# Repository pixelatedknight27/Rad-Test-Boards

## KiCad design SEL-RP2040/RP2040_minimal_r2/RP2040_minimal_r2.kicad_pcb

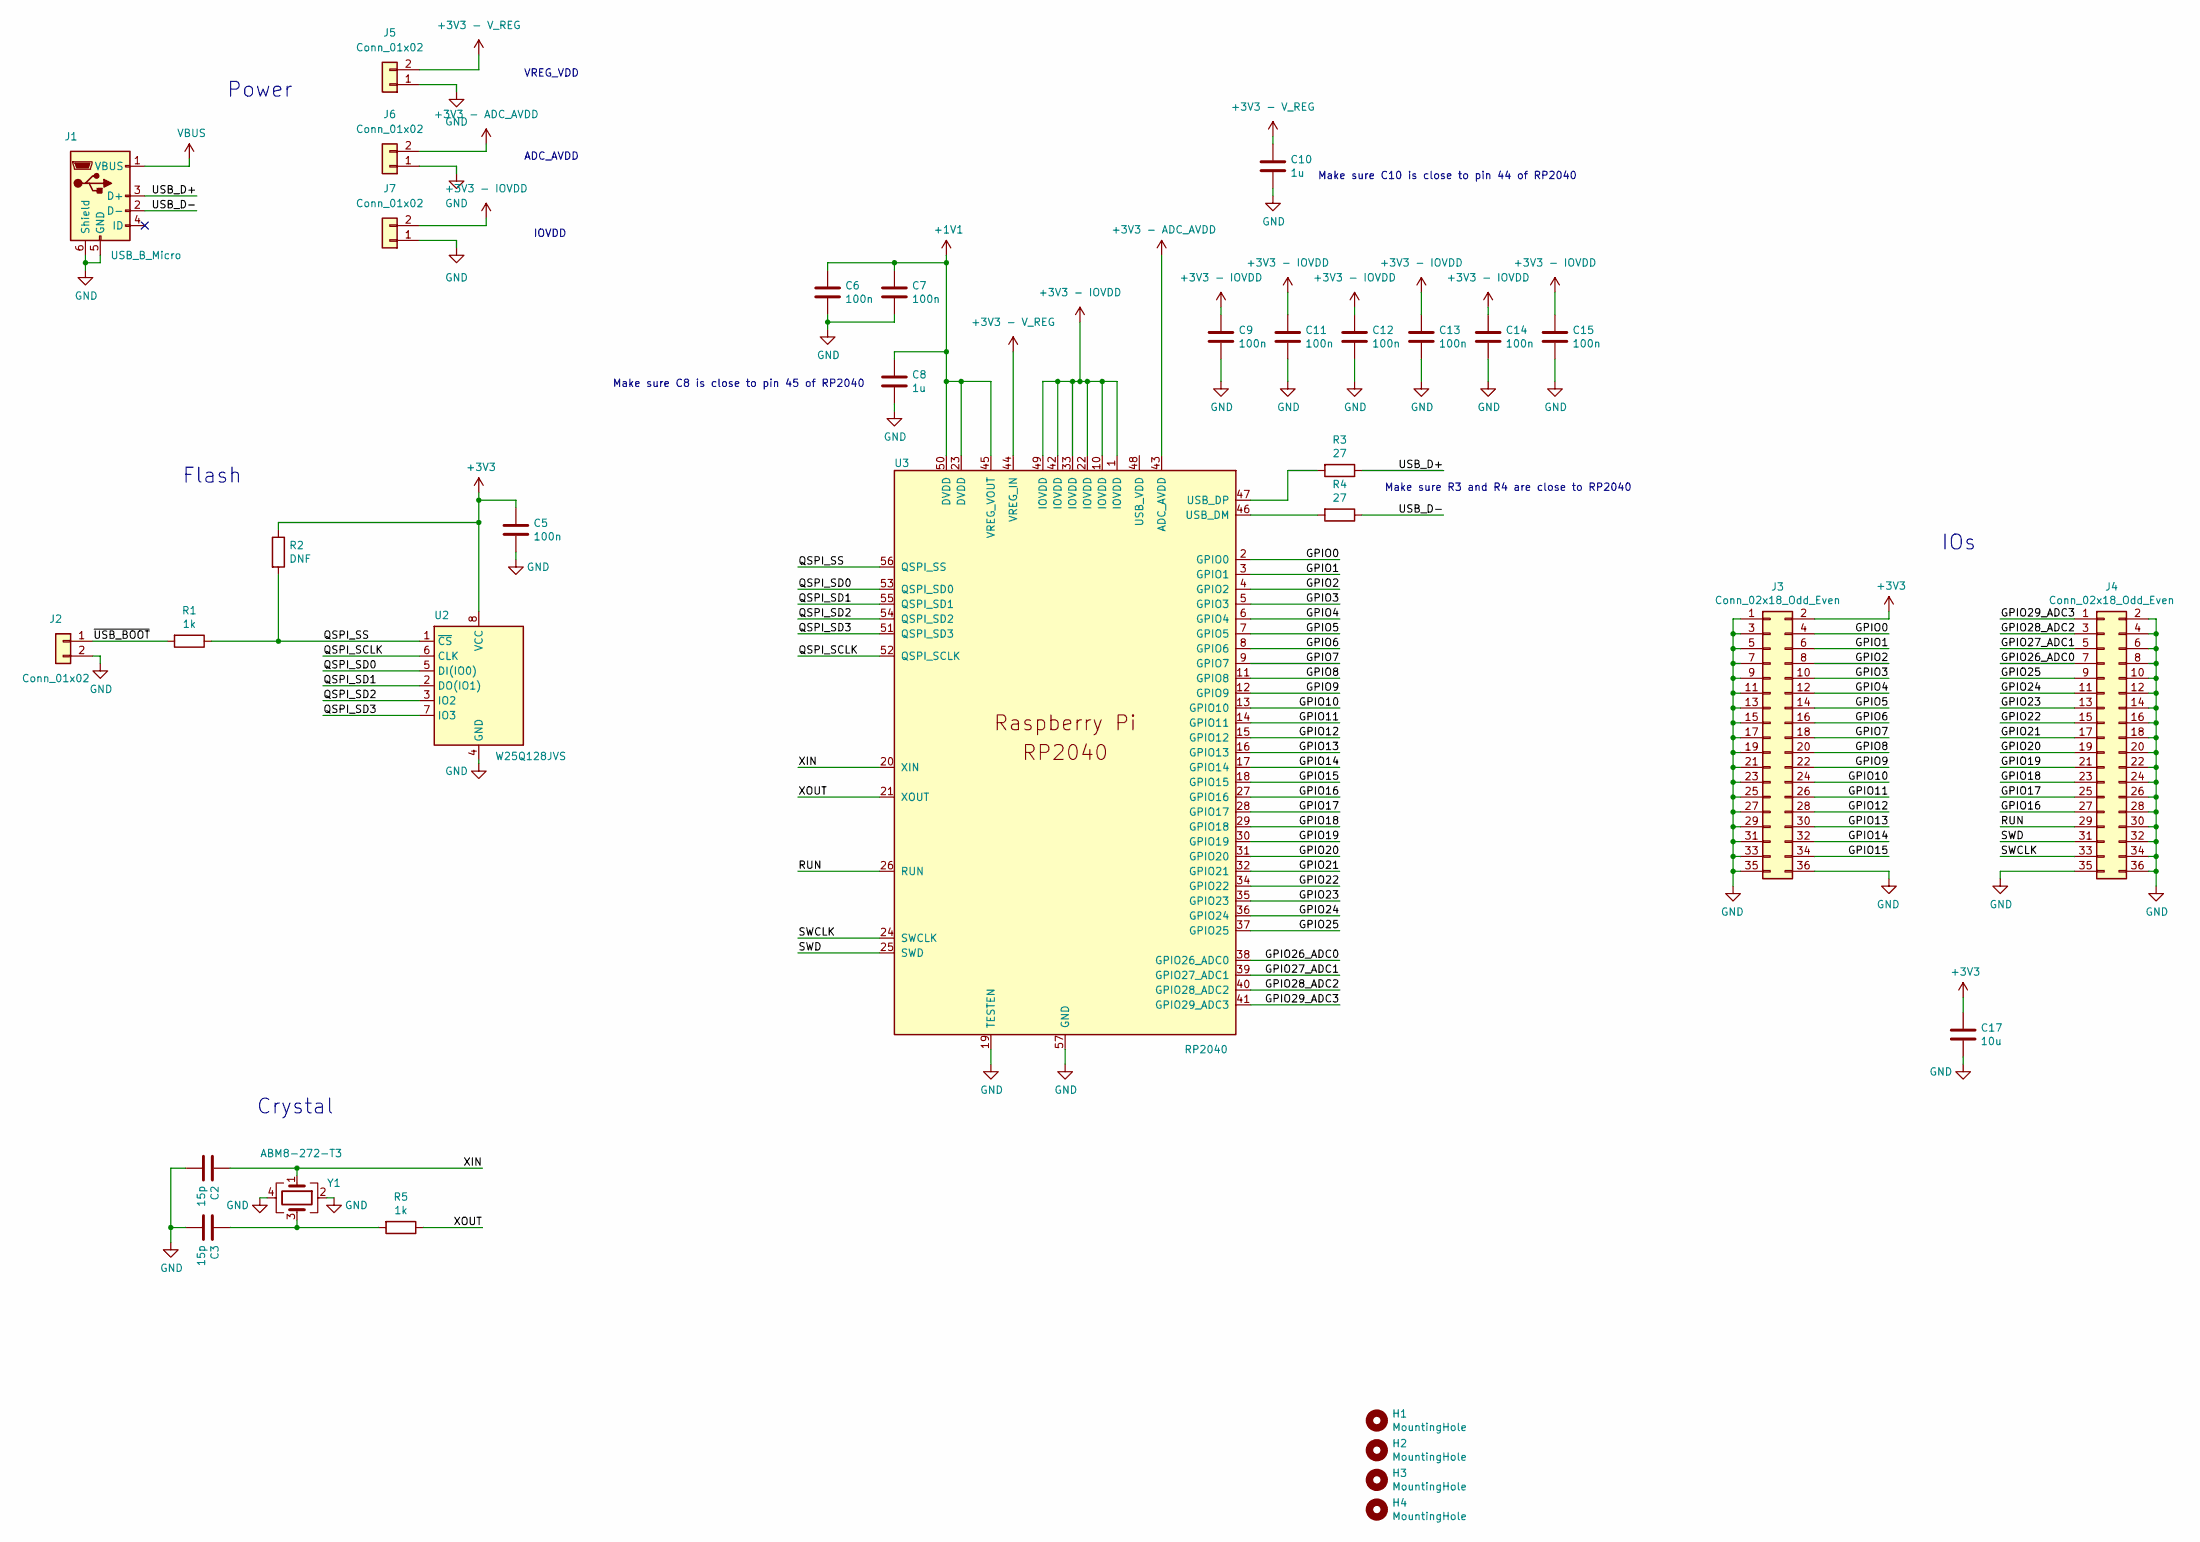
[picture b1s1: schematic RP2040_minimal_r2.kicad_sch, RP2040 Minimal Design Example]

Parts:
C2, C3: 15p; C_0402_1005Metric
C5, C6, C7, C9, C11, C12, C13, C14, C15: 100n; C_0402_1005Metric
C8, C10: 1u; C_0402_1005Metric
C17: 10u; C_0805_2012Metric
H1, H2, H3, H4: MountingHole; MountingHole_2.7mm_M2.5
J1: USB_B_Micro; USB_Micro-B_Amphenol_10103594-0001LF_Horizontal_modified
J2, J5, J6, J7: Conn_01x02; PinHeader_1x02_P2.54mm_Vertical
J3, J4: Conn_02x18_Odd_Even; PinHeader_2x18_P2.54mm_Vertical
R1, R5: 1k; R_0402_1005Metric
R2: DNF; R_0402_1005Metric
R3, R4: 27; R_0402_1005Metric
U2: W25Q128JVS; SOIC-8_5.23x5.23mm_P1.27mm
U3: RP2040; RP2040-QFN-56
Y1: ABM8-272-T3; Crystal_SMD_3225-4Pin_3.2x2.5mm

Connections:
+1V1: C6.1, C7.1, C8.1, U3.23 (DVDD), U3.45 (VREG_VOUT), U3.50 (DVDD)
+3V3: C5.1, C17.1, J3.2, R2.1, U2.8 (VCC)
+3V3 - ADC_AVDD: J6.2, U3.43 (ADC_AVDD)
+3V3 - IOVDD: C9.1, C11.1, C12.1, C13.1, C14.1, C15.1, J7.2, U3.1 (IOVDD), U3.10 (IOVDD), U3.22 (IOVDD), U3.33 (IOVDD), U3.42 (IOVDD), U3.49 (IOVDD)
+3V3 - V_REG: C10.1, J5.2, U3.44 (VREG_IN)
/GPIO0: J3.4, U3.2 (GPIO0)
/GPIO1: J3.6, U3.3 (GPIO1)
/GPIO2: J3.8, U3.4 (GPIO2)
/GPIO3: J3.10, U3.5 (GPIO3)
/GPIO4: J3.12, U3.6 (GPIO4)
/GPIO5: J3.14, U3.7 (GPIO5)
/GPIO6: J3.16, U3.8 (GPIO6)
/GPIO7: J3.18, U3.9 (GPIO7)
/GPIO8: J3.20, U3.11 (GPIO8)
/GPIO9: J3.22, U3.12 (GPIO9)
/GPIO10: J3.24, U3.13 (GPIO10)
/GPIO11: J3.26, U3.14 (GPIO11)
/GPIO12: J3.28, U3.15 (GPIO12)
/GPIO13: J3.30, U3.16 (GPIO13)
/GPIO14: J3.32, U3.17 (GPIO14)
/GPIO15: J3.34, U3.18 (GPIO15)
/GPIO16: J4.27, U3.27 (GPIO16)
/GPIO17: J4.25, U3.28 (GPIO17)
/GPIO18: J4.23, U3.29 (GPIO18)
/GPIO19: J4.21, U3.30 (GPIO19)
/GPIO20: J4.19, U3.31 (GPIO20)
/GPIO21: J4.17, U3.32 (GPIO21)
/GPIO22: J4.15, U3.34 (GPIO22)
/GPIO23: J4.13, U3.35 (GPIO23)
/GPIO24: J4.11, U3.36 (GPIO24)
/GPIO25: J4.9, U3.37 (GPIO25)
/GPIO26_ADC0: J4.7, U3.38 (GPIO26_ADC0)
/GPIO27_ADC1: J4.5, U3.39 (GPIO27_ADC1)
/GPIO28_ADC2: J4.3, U3.40 (GPIO28_ADC2)
/GPIO29_ADC3: J4.1, U3.41 (GPIO29_ADC3)
/QSPI_SCLK: U2.6 (CLK), U3.52 (QSPI_SCLK)
/QSPI_SD0: U2.5 (DI(IO0)), U3.53 (QSPI_SD0)
/QSPI_SD1: U2.2 (DO(IO1)), U3.55 (QSPI_SD1)
/QSPI_SD2: U2.3 (IO2), U3.54 (QSPI_SD2)
/QSPI_SD3: U2.7 (IO3), U3.51 (QSPI_SD3)
/QSPI_SS: R1.1, R2.2, U2.1 (~CS), U3.56 (QSPI_SS)
/RUN: J4.29, U3.26 (RUN)
/SWCLK: J4.33, U3.24 (SWCLK)
/SWD: J4.31, U3.25 (SWD)
/USB_D+: J1.3 (D+), R3.1
/USB_D-: J1.2 (D-), R4.1
/XIN: C2.1, U3.20 (XIN), Y1.1
/XOUT: R5.1, U3.21 (XOUT)
/~USB_BOOT: J2.1, R1.2
GND: C2.2, C3.2, C5.2, C6.2, C7.2, C8.2, C9.2, C10.2, C11.2, C12.2, C13.2, C14.2, C15.2, C17.2, J1.5 (GND), J1.6 (Shield), J2.2, J3.1, J3.3, J3.5, J3.7, J3.9, J3.11, J3.13, J3.15, J3.17, J3.19, J3.21, J3.23, J3.25, J3.27, J3.29, J3.31, J3.33, J3.35, J3.36, J4.2, J4.4, J4.6, J4.8, J4.10, J4.12, J4.14, J4.16, J4.18, J4.20, J4.22, J4.24, J4.26, J4.28, J4.30, J4.32, J4.34, J4.35, J4.36, J5.1, J6.1, J7.1, U2.4 (GND), U3.19 (TESTEN), U3.57 (GND), Y1.2, Y1.4
unnamed: C3.1, R5.2, Y1.3
unnamed: R4.2, U3.46 (USB_DM)
unnamed: R3.2, U3.47 (USB_DP)
VBUS: J1.1 (VBUS)

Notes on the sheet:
IOs
Power
Crystal
Make sure C8 is close to pin 45 of RP2040
ADC_AVDD
VREG_VDD
Make sure C10 is close to pin 44 of RP2040
Make sure R3 and R4 are close to RP2040
IOVDD
Flash

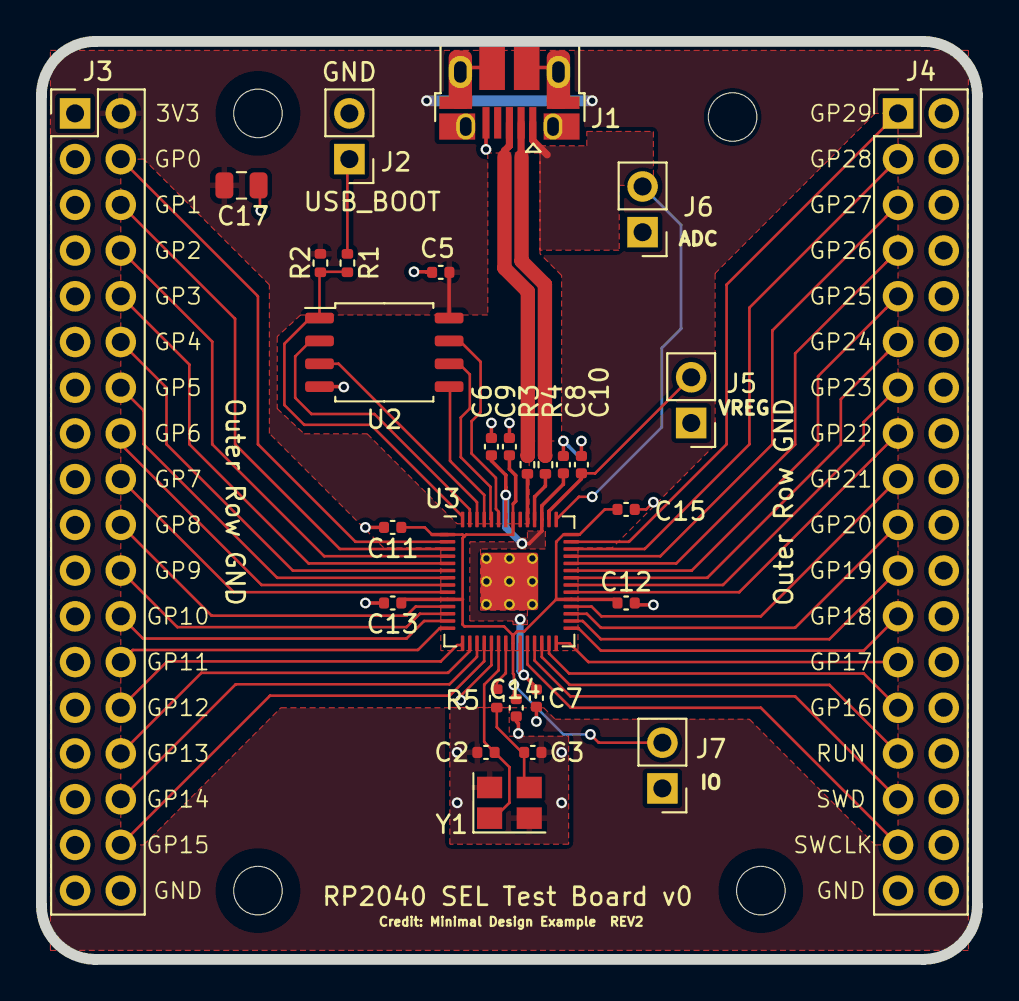
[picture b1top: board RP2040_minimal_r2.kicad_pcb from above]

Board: 2 copper layers, 52.0 x 51.0 mm, 33 parts (0 on the bottom side), 53 nets.

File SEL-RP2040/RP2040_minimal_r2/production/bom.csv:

Designator,Footprint,Quantity,Value,LCSC Part #
"C10, C8",0402,2,1u,
"C11, C12, C13, C14, C15, C5, C6, C7, C9",0402,9,100n,
C17,0805,1,10u,
"C2, C3",0402,2,15p,
"H1, H2, H3, H4",MountingHole_2.7mm_M2.5,4,MountingHole,
J1,USB_Micro-B_Amphenol_10103594-0001LF_Horizontal_modified,1,USB_B_Micro,
"J2, J5, J6, J7",PinHeader_1x02_P2.54mm_Vertical,4,Conn_01x02,
"J3, J4",PinHeader_2x18_P2.54mm_Vertical,2,Conn_02x18_Odd_Even,
"R1, R5",0402,2,1k,
R2,0402,1,DNF,
"R3, R4",0402,2,27,
U2,SOIC-8_5.23x5.23mm_P1.27mm,1,W25Q128JVS,
U3,RP2040-QFN-56,1,RP2040,
Y1,Crystal_SMD_3225-4Pin_3.2x2.5mm,1,ABM8-272-T3,

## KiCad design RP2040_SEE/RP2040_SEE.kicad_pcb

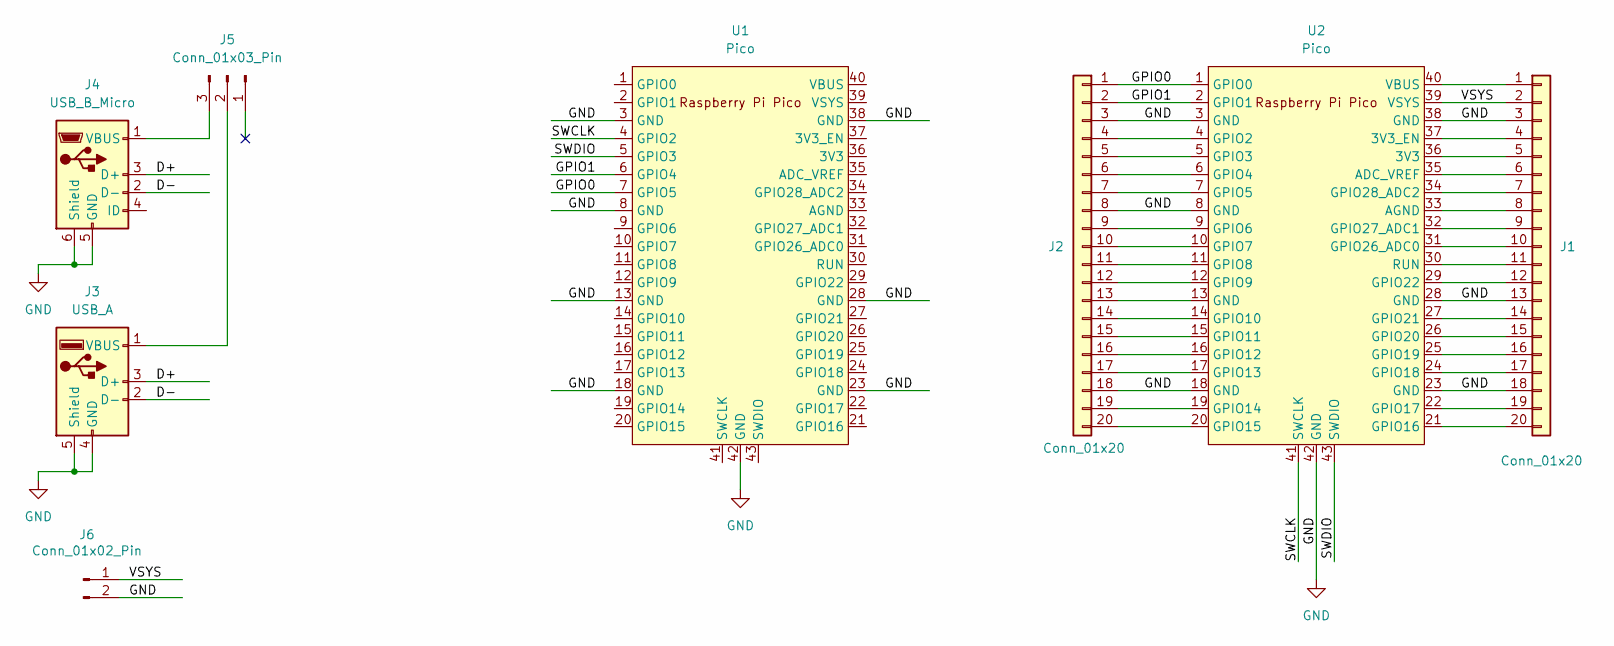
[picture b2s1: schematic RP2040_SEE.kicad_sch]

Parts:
J1, J2: Conn_01x20; PinSocket_1x20_P2.54mm_Vertical
J3: USB_A; USB_A_TE_292303-7_Horizontal
J4: USB_B_Micro; USB_Micro-B_Amphenol_10103594-0001LF_Horizontal
J5: Conn_01x03_Pin; PinHeader_1x03_P2.54mm_Vertical
J6: Conn_01x02_Pin; PinHeader_1x02_P2.54mm_Vertical
U1, U2: Pico; RPi_Pico_SMD_TH

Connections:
/D+: J3.3 (D+), J4.3 (D+)
/D-: J3.2 (D-), J4.2 (D-)
/GPIO0: J2.1, U1.7 (GPIO5), U2.1 (GPIO0)
/GPIO1: J2.2, U1.6 (GPIO4), U2.2 (GPIO1)
/SWCLK: U1.4 (GPIO2), U2.41 (SWCLK)
/SWDIO: U1.5 (GPIO3), U2.43 (SWDIO)
/VSYS: J1.2, J6.1, U2.39 (VSYS)
GND: J1.3, J1.13, J1.18, J2.3, J2.8, J2.18, J3.4 (GND), J3.5 (Shield), J4.5 (GND), J4.6 (Shield), J6.2, U1.3 (GND), U1.8 (GND), U1.13 (GND), U1.18 (GND), U1.23 (GND), U1.28 (GND), U1.38 (GND), U1.42 (GND), U2.3 (GND), U2.8 (GND), U2.18 (GND), U2.23 (GND), U2.28 (GND), U2.38 (GND), U2.42 (GND)
unnamed: J1.1, U2.40 (VBUS)
unnamed: J1.4, U2.37 (3V3_EN)
unnamed: J1.5, U2.36 (3V3)
unnamed: J1.6, U2.35 (ADC_VREF)
unnamed: J1.7, U2.34 (GPIO28_ADC2)
unnamed: J1.8, U2.33 (AGND)
unnamed: J1.9, U2.32 (GPIO27_ADC1)
unnamed: J1.10, U2.31 (GPIO26_ADC0)
unnamed: J1.11, U2.30 (RUN)
unnamed: J1.12, U2.29 (GPIO22)
unnamed: J1.14, U2.27 (GPIO21)
unnamed: J1.15, U2.26 (GPIO20)
unnamed: J1.16, U2.25 (GPIO19)
unnamed: J1.17, U2.24 (GPIO18)
unnamed: J1.19, U2.22 (GPIO17)
unnamed: J1.20, U2.21 (GPIO16)
unnamed: J2.4, U2.4 (GPIO2)
unnamed: J2.5, U2.5 (GPIO3)
unnamed: J2.6, U2.6 (GPIO4)
unnamed: J2.7, U2.7 (GPIO5)
unnamed: J2.9, U2.9 (GPIO6)
unnamed: J2.10, U2.10 (GPIO7)
unnamed: J2.11, U2.11 (GPIO8)
unnamed: J2.12, U2.12 (GPIO9)
unnamed: J2.13, U2.13 (GND)
unnamed: J2.14, U2.14 (GPIO10)
unnamed: J2.15, U2.15 (GPIO11)
unnamed: J2.16, U2.16 (GPIO12)
unnamed: J2.17, U2.17 (GPIO13)
unnamed: J2.19, U2.19 (GPIO14)
unnamed: J2.20, U2.20 (GPIO15)
unnamed: J3.1 (VBUS), J5.2
unnamed: J4.1 (VBUS), J5.3

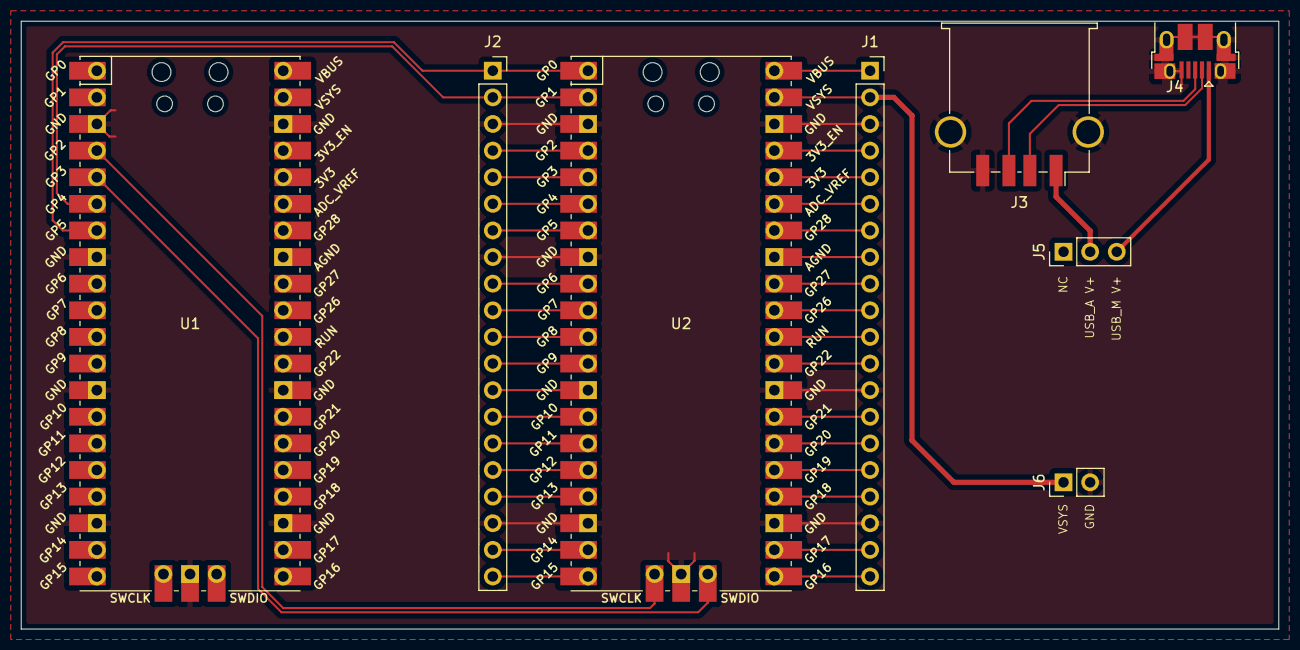
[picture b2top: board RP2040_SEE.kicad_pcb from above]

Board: 2 copper layers, 120.0 x 58.0 mm, 8 parts (0 on the bottom side), 41 nets.

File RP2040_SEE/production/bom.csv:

Designator,Footprint,Quantity,Value,LCSC Part #
"J1, J2",PinSocket_1x20_P2.54mm_Vertical,2,Conn_01x20,
J3,USB_A_TE_292303-7_Horizontal,1,USB_A,
J4,USB_Micro-B_Amphenol_10103594-0001LF_Horizontal,1,USB_B_Micro,
J5,PinHeader_1x03_P2.54mm_Vertical,1,Conn_01x03_Pin,
J6,PinHeader_1x02_P2.54mm_Vertical,1,Conn_01x02_Pin,
"U1, U2",RPi_Pico_SMD_TH,2,Pico,

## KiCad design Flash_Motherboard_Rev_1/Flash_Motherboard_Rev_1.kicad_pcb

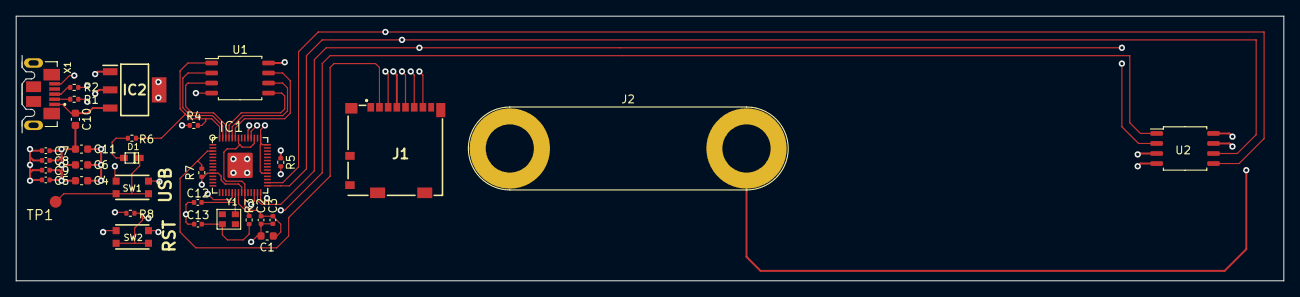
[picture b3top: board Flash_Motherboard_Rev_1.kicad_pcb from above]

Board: 4 copper layers, 160.5 x 33.5 mm, 33 parts (0 on the bottom side), 26 nets.

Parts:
C1, C4, C6: 1uF; C_0603_1608Metric
C2, C3, C5, C7, C8, C9: 0.1uF; C_0402_1005Metric
C10: 10uF; C_0603_1608Metric
C11: 22uF; C_0603_1608Metric
C12, C13: 22pF; C_0402_1005Metric
D1: NSR0320; SOD-323F
IC1: RP2040_QFN56; QFN56_7MM_REDUCEDEPAD
IC2: AZ1117CH-3.3TRG1; SOT230P700X180-4N
J1: 104031-0811; 1040310811
J2: Power Supply banannanan; Banana_Jack_2Pin
R1, R2: 22; R_0402_1005Metric
R3: 1k; R_0402_1005Metric
R4, R5, R7: 10k; R_0402_1005Metric
R6: 1K; R_0402_1005Metric
R8: 10K; R_0402_1005Metric
SW1, SW2: KMR2; BTN_KMR2_4.6X2.8
TP1: TESTPOINTROUND1.5MMNO; TESTPOINT_ROUND_1.5MM_NO
U1, U2: W25Q128JV; SOIC-8_5.275x5.275mm_P1.27mm
X1: microUSB; MOLEX_105164-0001
Y1: 12MHZ; CRYSTAL_2.5X2

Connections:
1.2V: C1.1, C2.2, C3.2, IC1.23 (DVDD), IC1.45 (VREG_VOUT), IC1.50 (DVDD)
+3V3: C4.1, C5.1, C6.1, C7.1, C8.1, C9.1, C11.1, IC1.1 (IOVDD), IC1.10 (IOVDD), IC1.22 (IOVDD), IC1.33 (IOVDD), IC1.42 (IOVDD), IC1.43 (ADC_IOVDD), IC1.44 (VREG_IOVDD), IC1.48 (USB_IOVDD), IC1.49 (IOVDD), IC2.2 (OUTPUT), IC2.4 (VOUT), J1.4 (VDD), R4.1, R5.2, R7.2, R8.1, U1.8 (VCC), U2.3 (WP#/IO2), U2.7 (HOLD#/IO3)
/D+: IC1.47 (USB_D+), R1.2
/D-: IC1.46 (USB_D-), R2.2
/QSPI_CS: IC1.56 (~QSPI_CS), R4.2, R6.1, U1.1 (SSEL)
/QSPI_SCLK: IC1.52 (QSPI_SCLK), U1.6 (SCK)
/QSPI_SD0: IC1.53 (QSPI_SD0), U1.5 (MOSI)
/QSPI_SD1: IC1.55 (QSPI_SD1), U1.2 (MISO)
/QSPI_SD2: IC1.54 (QSPI_SD2), U1.3 (WP#/IO2)
/QSPI_SD3: IC1.51 (QSPI_SD3), U1.7 (HOLD#/IO3)
/USBBOOT: D1.C, SW1.A, SW1.A' (P1), TP1.P$1
/~RESET: IC1.26 (/RUN), R8.2, SW2.A, SW2.A' (P1)
GND: C1.2, C2.1, C3.1, C4.2, C5.2, C6.2, C7.2, C8.2, C9.2, C10.2, C11.2, C12.1, C13.1, IC1.19 (TESTEN), IC1.P$1 (GND), IC2.1 (ADJ/GND), J1.6 (VSS), J2.1, SW1.B (S), SW1.B' (S1), SW2.B (S), SW2.B' (S1), U1.4 (VSS), U2.4 (VSS), X1.5 (GND)
unnamed: C13.2, R3.1, Y1.1
unnamed: D1.A, R6.2
unnamed: C12.2, IC1.20 (XIN), Y1.3 (2)
unnamed: IC1.21 (XOUT), R3.2
unnamed: J2.2, U2.8 (VCC)
unnamed: R1.1, X1.2 (D+)
unnamed: R2.1, X1.3 (D-)
SPI0_CS0: IC1.28 (GPIO17), R5.1, U2.1 (SSEL)
SPI0_CS1: IC1.3 (GPIO1), J1.2 (CD/DAT3), R7.1
SPI0_MISO: IC1.27 (GPIO16), J1.7 (DAT0), U2.2 (MISO)
SPI0_MOSI: IC1.30 (GPIO19), J1.3 (CMD), U2.5 (MOSI)
SPI0_SCK: IC1.29 (GPIO18), J1.5 (CLK), U2.6 (SCK)
VBUS: C10.1, IC2.3 (INPUT), X1.1 (VBUS)

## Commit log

2024-02-28 Formatting
2024-05-24 Added reset line to rp2040
2024-05-28 All Footprints Added
2024-05-30 Routing
2024-05-30 Routing Autosave
2024-05-30 More Routing Autosave
2024-05-30 Last one I swear
2024-05-30 Routing Almost Complete
2024-05-30 Closing it out
2024-05-31 Banananna
2024-06-09 renaming
2024-06-11 Rev 2 almost done
2024-06-12 Routing Done
2024-06-12 ready for review
2024-06-12 more autosave
2024-08-17 ooga booga
2024-08-18 banana phone
2024-08-18 RP2040 Minimal
